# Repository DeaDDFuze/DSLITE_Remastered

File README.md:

# DSLITE_Remastered

> A modern hardware rework of the Nintendo DS Lite.

**DSLITE_Remastered** is an experimental hardware engineering project aiming to recreate and modernize the Nintendo DS Lite while preserving compatibility with the original console, cartridges, controls and overall form factor.

The goal is not to emulate a Nintendo DS on a modern computer.

The goal is to understand the original hardware, reverse-engineer it where necessary, redesign selected parts of the electronics, and progressively build a **modernized DS Lite around the original architecture**.

---

## Project goals

DSLITE_Remastered explores several areas of console hardware modernization:

- Reverse engineering of the Nintendo DS Lite motherboard
- Recreation of schematics in KiCad
- PCB analysis and eventual PCB redesign
- Replacement of ageing or obsolete components
- USB-C charging
- Modern battery and charging circuitry
- Improved power management
- Modern replacement displays
- Experimental display scaling / image processing
- Replacement shells and mechanical parts
- 3D CAD reconstruction of the console
- Improved repairability
- Hardware documentation
- Community-friendly component libraries

The project will remain modular so individual modifications can potentially be reproduced independently.

---

## Project philosophy

The idea behind DSLITE_Remastered is simple:

**repair, understand, reproduce, improve.**

Rather than replacing the entire console with a Raspberry Pi or an emulator, this project attempts to retain as much of the original Nintendo DS architecture as possible.

Whenever possible, the project will favor:

- original hardware compatibility;
- measurable and documented modifications;
- replaceable components;
- open design files;
- commonly available parts;
- reproducible modifications;
- preservation of the original console's behaviour.

Some parts of the project will necessarily remain experimental.

---

## Planned architecture

The long-term project may include several independent hardware modules.

### Main motherboard

Reverse engineering and recreation of the Nintendo DS Lite motherboard.

Current reference board:

`USG-CPU-10`

Objectives:

- reproduce the original schematic;
- identify component functions;
- document power rails;
- document buses and signals;
- recreate footprints;
- compare component revisions;
- prepare a possible redesigned motherboard.

---

### Power system

Potential improvements:

- USB-C connector;
- USB-C charging;
- modern Li-ion / Li-Po battery support;
- improved battery protection;
- improved charging controller;
- voltage monitoring;
- replaceable battery design.

USB Power Delivery is not currently required for the console but may be investigated for future accessories or docking concepts.

---

### Displays

One of the major experimental areas of the project.

Possible directions include:

- modern IPS LCD replacements;
- custom LCD interface boards;
- OLED experimentation;
- improved brightness;
- improved viewing angles;
- replacement backlight circuitry.

The native Nintendo DS resolution remains:

**256 × 192 pixels per screen**

A future experimental display controller may investigate integer scaling or real-time upscaling to higher-resolution panels.

---

## DS Remastered display concept

A more experimental branch of the project explores the concept of a **"DS Remastered" display pipeline**.

Instead of modifying the game software, a dedicated video-processing circuit could intercept the original display signal and process it before sending it to a modern panel.

Conceptually:

```text
Nintendo DS GPU
      │
      ▼
Original display signal
      │
      ▼
Video capture / interface
      │
      ▼
FPGA / video processor
      │
      ├── Integer scaling
      ├── Filtering
      ├── Pixel reconstruction
      └── Experimental upscaling
      │
      ▼
Modern LCD / OLED panel
```

The first realistic objective would be **clean integer scaling**, not AI-based reconstruction.

More advanced processing may be investigated later.

---

## Mechanical redesign

The mechanical side of the project will be developed primarily using **Fusion 360**.

Possible work includes:

- recreation of the DS Lite shell;
- internal mounting points;
- USB-C modifications;
- display adapters;
- replacement hinge mechanisms;
- battery compartment redesign;
- custom shells;
- prototype PCBs;
- 3D printable replacement parts.

KiCad remains the primary tool for electronic design.

---

## Software used

### Electronics

- KiCad
- SPICE simulation where appropriate
- Datasheets
- Multimeter
- Logic analyser
- Oscilloscope

### Mechanical design

- Autodesk Fusion 360
- Mesh / STEP / STL tools
- 3D printing

### Development / documentation

- Git
- GitHub
- Linux
- Markdown
- Python

---

## Repository structure

The repository will progressively follow a structure similar to:

```text
DSLITE_Remastered/
│
├── README.md
├── LICENSE
│
├── docs/
│   ├── architecture/
│   ├── reverse-engineering/
│   ├── measurements/
│   └── research/
│
├── datasheets/
│
├── schematic/
│   ├── original/
│   └── remastered/
│
├── pcb/
│   ├── original/
│   └── remastered/
│
├── libraries/
│   ├── symbols/
│   ├── footprints/
│   └── 3dmodels/
│
├── mechanical/
│   ├── shell/
│   ├── screen/
│   └── usb-c/
│
├── firmware/
│
├── tools/
│
└── references/
```

This structure may change as the project evolves.

---

## Current project status

**Status: Research / Reverse Engineering**

Current work focuses on:

- collecting DS Lite motherboard documentation;
- analysing the `USG-CPU-10` board revision;
- identifying components;
- collecting datasheets;
- reconstructing schematics;
- creating reusable KiCad symbols and footprints;
- preparing a clean Git repository structure.

No complete replacement motherboard exists yet.

---

## Roadmap

### Phase 1 — Documentation

- [ ] Photograph and document the motherboard
- [ ] Identify major ICs
- [ ] Identify passive components
- [ ] Collect datasheets
- [ ] Document test points
- [ ] Document connectors
- [ ] Map power rails

### Phase 2 — Schematic reconstruction

- [ ] Recreate `USG-CPU-10` schematics
- [ ] Verify connections
- [ ] Create missing KiCad symbols
- [ ] Create missing footprints
- [ ] Compare board revisions

### Phase 3 — PCB reconstruction

- [ ] Recreate PCB outline
- [ ] Position major components
- [ ] Reconstruct routing
- [ ] Validate dimensions
- [ ] Generate 3D PCB model

### Phase 4 — Modernization

- [ ] USB-C charging
- [ ] Modern battery circuitry
- [ ] Modern replacement displays
- [ ] Improved power circuitry
- [ ] Replacement shell design

### Phase 5 — DS Remastered experiments

- [ ] Capture original LCD signals
- [ ] Characterize timing
- [ ] Prototype FPGA display interface
- [ ] Integer-scale DS output
- [ ] Test higher-resolution panels
- [ ] Investigate image enhancement

### Phase 6 — Prototype

- [ ] Manufacture prototype PCBs
- [ ] Assemble board
- [ ] Power validation
- [ ] Boot testing
- [ ] Cartridge testing
- [ ] Touchscreen testing
- [ ] Wireless testing
- [ ] Long-term reliability testing

---

## Reverse engineering notes

All measurements and reverse-engineering information should be documented whenever possible.

Useful information includes:

```text
Component reference
Manufacturer
Part number
Package
Measured value
Connected signals
Voltage
Frequency
Datasheet
Board location
Notes
```

This repository should progressively become both a development repository and a technical reference for DS Lite hardware.

---

## KiCad libraries

One objective of the project is to create a reusable local KiCad library for DS Lite components.

Example:

```text
libraries/
├── symbols/
│   └── DSLITE_Remastered.kicad_sym
│
├── footprints/
│   └── DSLITE_Remastered.pretty/
│
└── 3dmodels/
    ├── STEP/
    └── WRL/
```

Components should preferably include:

- symbol;
- footprint;
- datasheet reference;
- manufacturer part number;
- package;
- pin description;
- 3D model when available.

---

## Contributions

Contributions are welcome.

Useful contributions include:

- board photographs;
- high-resolution scans;
- component identification;
- datasheets;
- PCB measurements;
- schematics;
- KiCad symbols;
- KiCad footprints;
- 3D models;
- electrical measurements;
- compatible replacement components;
- repair documentation.

Please document the source of technical information whenever possible.

---

## Disclaimer

DSLITE_Remastered is an independent, unofficial hardware research project.

Nintendo, Nintendo DS, Nintendo DS Lite and related trademarks are property of Nintendo and their respective owners.

This project is not affiliated with, endorsed by, or sponsored by Nintendo.

The repository is intended for:

- hardware research;
- repair;
- preservation;
- reverse engineering;
- education;
- experimentation.

No proprietary Nintendo software, firmware, ROMs or copyrighted game assets should be distributed through this repository.

---

## License

The final licensing model has not yet been selected.

Because the project may contain hardware designs, documentation and software, separate licenses may eventually be used for each category.

Possible choices include:

- CERN Open Hardware Licence for PCB and hardware designs
- GPL or MIT for software and tools
- Creative Commons for documentation

---

## Project name

**DSLITE_Remastered**

Experimental Nintendo DS Lite hardware modernization and preservation project.

```text
Original hardware.
Modern components.
Same DS.
```

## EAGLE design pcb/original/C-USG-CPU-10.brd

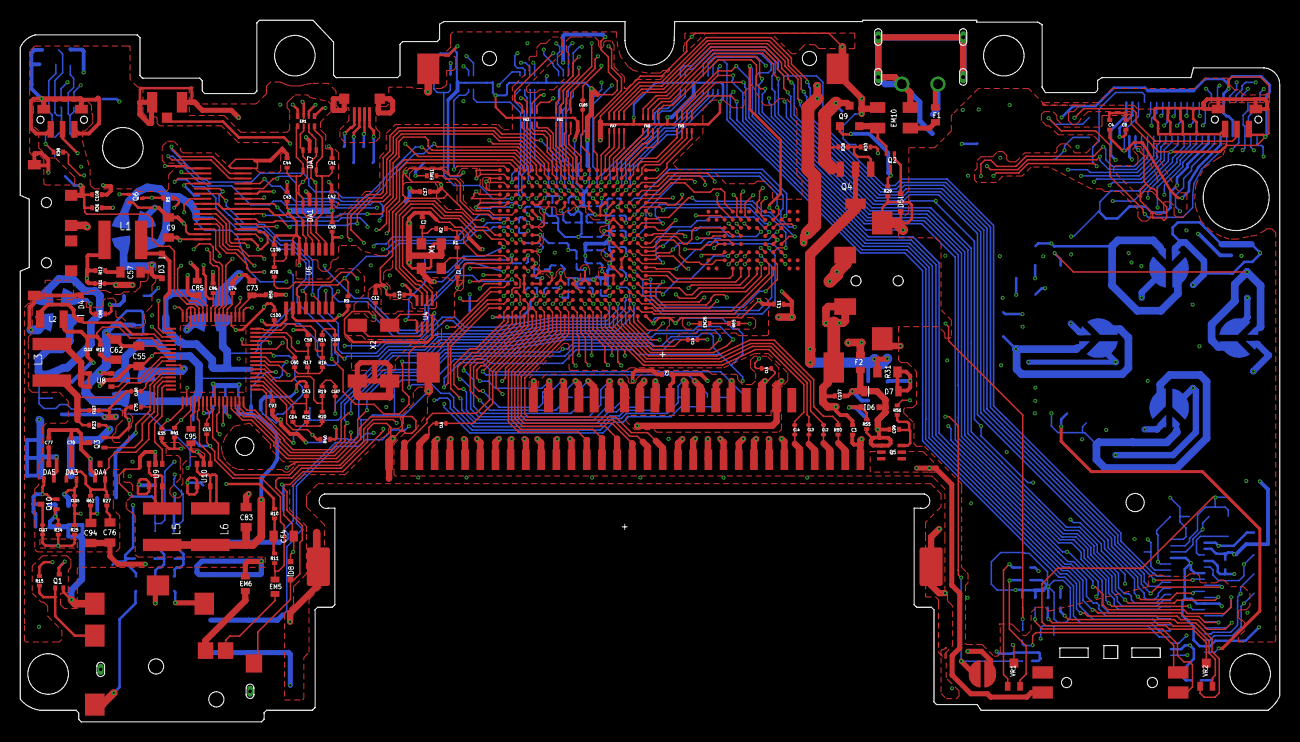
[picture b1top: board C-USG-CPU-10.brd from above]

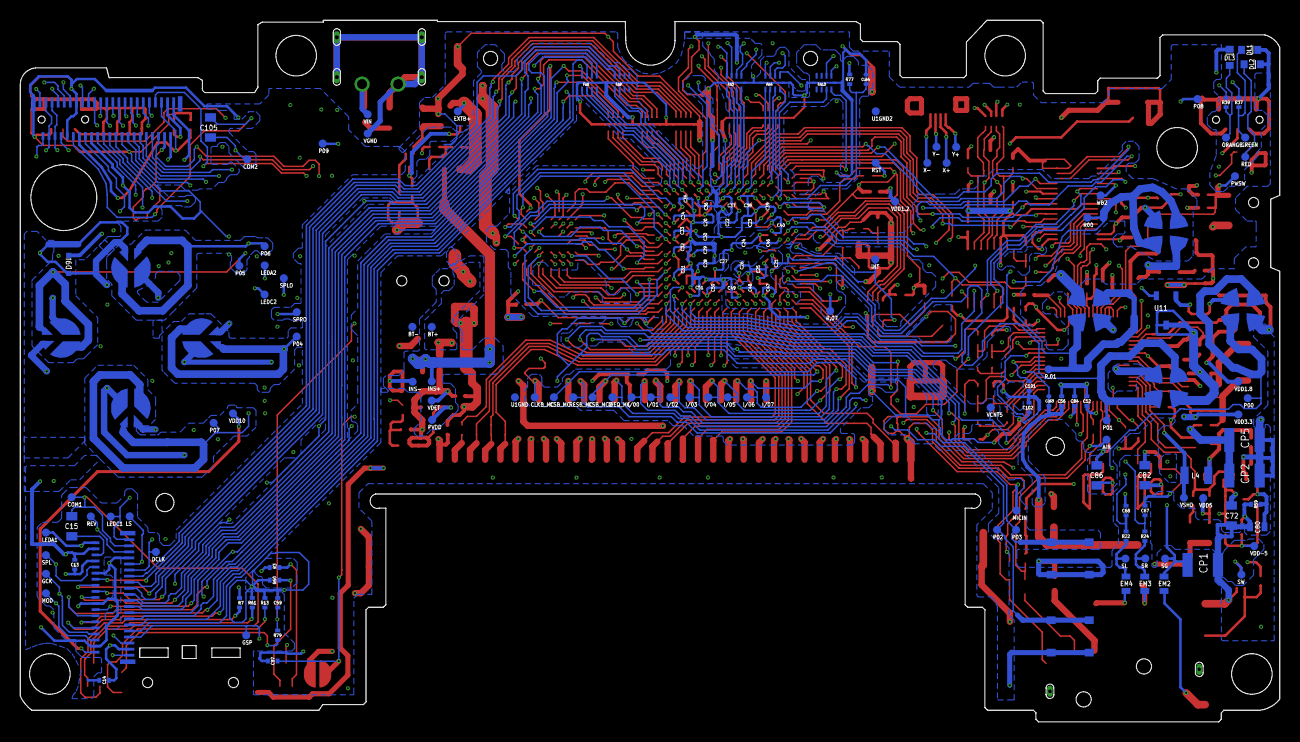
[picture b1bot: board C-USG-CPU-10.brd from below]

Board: 6 copper layers, 124.3 x 69.2 mm, 319 parts (164 on the bottom side), 328 nets.

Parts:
AIN: TP
BT+: TP
BT-: TP
BUT_A: BUT_ABXY; BUTTONSABXY
BUT_B: BUT_ABXY; BUTTONSABXY
BUT_L: SHOULDER_BUT
BUT_R: SHOULDER_BUT
BUT_X: BUT_ABXY; BUTTONSABXY
BUT_Y: BUT_ABXY; BUTTONSABXY
C1, C2, C3, C4, C5, C6, C10, C11, C12, C13, C14, C17, C41, C42, C43, C44, C45, C52, C53, C56, C58, C59, C60, C63, C64, C67, C68, C70, C74, C75, C77, C84, C88, C93, C96, C97, C99, C100, C101, C102, C106, C107, C108: C0402; 0402
C9, C15, C54, C55, C57, C62, C72, C76, C82, C83, C86, C94, C105: C0805; 0805
C20, C21, C22, C23, C24, C25, C26, C27, C28, C29, C30, C31, C32, C33, C34, C35, C36, C37, C38, C39, C40, C46, C47, C48, C49, C50, C51: C0201; 0201
C73, C80, C85, C95: C0603; 0603
CL2, CL3, CL4, CL5, CL6, CL9, CL11, CL12, CL13, CL15, CL17, CL60, CL63, CL64, CL65, CL67, CL68: CL; CL0402
CLKB_MC: TP
COM1, COM2: TP
CP1, CP2, CP5: CP
CSB_MC, CSB_MC2: TP
D3, D4: D3.4
D5, D9: D5
D6: D6
D7: D7
D8: D8
DA1: MA5J002D; DA
DA3, DA4, DA5: MA3SD29F
DA7: MA5J002E; DA
DCLK: TP
DL1, DL2, DL3: DL
DOWN: DPAD
EM1: FILTER_NETWORK
EM2, EM3, EM4, EM5, EM6: FILTER0603; 0603
EM10: EM10
EM11, EM26: FILTER; 0402
EXTB+: TP
F1, F2: FUSE
FA1, FA2, FA3, FA4, FA5, FA6, FA7, FA8, FA9, FA10: FA
GCK: TP
GREEN: TP
GSP: TP
I/00, I/01, I/02, I/03, I/04, I/05, I/06, I/07: TP
INS+: TP
INS-: TP
INT: TP
IREQ_MC: TP
L1, L3, L5, L6: INDUCTOR
L2, L4: INDUCTOR_SMALL
LEDA1, LEDA2: TP
LEDC1, LEDC2: TP
LEFT: DPAD
LS: TP
MICIN: TP
MOD: TP
ORANGE: TP
P00, P01, P02, P03, P04, P05, P06, P07, P08, P09: TP
P.1: GBASLOT; GBA
P.2: DSSLOT; DS
P.3: TOP_SCR+SPK
P.4: BOTTOM_SCREEN
P.6: TOUCH; P6
P.7: BAT
P.8: HEADPHONES
P.9: CHARGEPORT
P.10: DWM-W006; DWM--W006
P.12: MIC
PVDD: TP
PWSW: TP
Q1: Q1
Q2: DTA143ZM; SOT723
Q3, Q10: SSM3K16FS; Q3.10
Q4: 2SA2069; SOT89-3
Q5: SSM6J21TU; UF6
Q6: 2SC4244; SOT723
Q9: SSM3J14T; TO236
R00, R.01, R.07: TP
R1, R2, R3, R5, R7, R9, R10, R11, R12, R13, R14, R15, R16, R17, R18, R19, R20, R21, R22, R23, R24, R25, R27, R28, R29, R30, R34, R35, R36, R37, R38, R39, R40, R41, R50, R55, R56, R59, R60, R61, R62, R65, R77, R78, R79, R80: R0402; 0402
R31: R0805; 0805
RED: TP
RESB_MC: TP
REV: TP
RIGHT: DPAD
RST: TP
SELECT: BUTTON_SMALL
SG: TP
SL: TP
SL1: SL1
SPL: TP
SPLO: TP
SPRO: TP
SR: TP
START: BUTTON_SMALL
SW: TP
SW13: SWITCH
U1: NTR_CPU_B; CPU
U1GND, U1GND2: TP
U2: 82DBS02163C-70L; RAM
U3: MITSUMI_3325A
U4: RTC; TSSOP8
U6: TSC2046; TSSOP16
U8: SSM5G04TU; SOT-353F___(UFV)-M
U9, U10: SSM5H08TU; SOT-353F___(UFV)-M
U11: EM6781
UP: DPAD
VCNT5: TP
VDD1.2, VDD1.8, VDD3.3, VDD5, VDD10: TP
VDD-5: TP
VDET: TP
VGND: TP
VIN: TP
VR1, VR2: VR
VR3: VOLUME
VSHD: TP
WB2: TP
X1: X1
X2: X2
X+: TP
X-: TP
Y+: TP
Y-: TP

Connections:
A16: P.1.22, U1.G17
A17: P.1.23, U1.H17
A18: P.1.24, U1.I17
A19: P.1.25, U1.J17
A20: P.1.26, U1.K17
A21: P.1.27, U1.L17
A22: P.1.28, U1.M17
A23: P.1.29, U1.N17
AD0: P.1.6, U1.G18
AD1: P.1.7, U1.G19
AD2: P.1.8, U1.H18
AD3: P.1.9, U1.H19
AD4: P.1.10, U1.I18
AD5: P.1.11, U1.I19
AD6: P.1.12, U1.J18
AD7: P.1.13, U1.J19
AD8: P.1.14, U1.K18
AD9: P.1.15, U1.K19
AD10: P.1.16, U1.L18
AD11: P.1.17, U1.L19
AD12: P.1.18, U1.M18
AD13: P.1.19, U1.M19
AD14: P.1.20, U1.N18
AD15: P.1.21, U1.N19
AIN: AIN.P$1, C53.2, EM5.1, R11.2
AUX: R78.1, U3.40
B+: C55.1, C56.2, C83.1, CL63.1, CL63.2, L5.P$2, L6.P$2, Q5.1, Q5.2, Q5.5, Q5.6, U3.16, U3.19, U3.23, U3.55, U8.2, VR3.3
B.B0: FA6.1, P.4.22
B.B1: FA7.7, P.4.23
B.B2: FA7.5, P.4.24
B.B3: FA7.3, P.4.25
B.B4: FA7.1, P.4.26
B.B5: FA9.3, P.4.27
B.G0: FA8.7, P.4.15
B.G1: FA6.5, P.4.16
B.G2: FA6.7, P.4.17
B.G3: FA8.5, P.4.19
B.G4: FA9.1, P.4.20
B.G5: FA6.3, P.4.21
B.R0: FA8.3, P.4.9
B.R1: FA8.1, P.4.10
B.R2: FA5.7, P.4.11
B.R3: FA5.3, P.4.12
B.R4: FA5.5, P.4.13
B.R5: FA5.1, P.4.14
BT+: BT+.P$1, F2.1, P.7.+
CLKB_MC: CL5.1, CL5.2, CLKB_MC.P$1, P.2.2, U1.T16
COM1: C15.1, COM1.P$1, P.4.37, VR2.2
COM2: C105.1, COM2.P$1, P.3.37, VR1.2
CS1B: CL4.1, CL4.2, P.1.5, U1.F19
CS2B: CL6.1, CL6.2, P.1.30, U1.O18
CSB_MC: CSB_MC.P$1, P.2.4, U1.S17
CSB_MC2: CSB_MC2.P$1, P.2.6, U1.P17
DCLK: DCLK.P$1, P.3.29, P.4.29, U1.G1
EXTB+: EXTB+.P$1, Q4.3, Q9.3, R28.1, R50.1
GCK: GCK.P$1, P.3.8, P.4.8, U1.H3
GND: BT-.P$1, BUT_A.1, BUT_A.4, BUT_B.1, BUT_B.4, BUT_L.1, BUT_L.3, BUT_L.S1, BUT_L.S2, BUT_R.1, BUT_R.3, BUT_R.S1, BUT_R.S2, BUT_X.1, BUT_X.4, BUT_Y.1, BUT_Y.4, C1.1, C2.2, C3.2, C4.2, C5.2, C6.1, C9.2, C10.2, C11.1, C12.1, C13.2, C14.2, C17.2, C20.2, C21.2, C22.2, C23.2, C24.2, C25.2, C26.2, C27.2, C28.2, C29.2, C30.2, C31.2, C32.2, C33.2, C34.2, C35.2, C36.2, C37.2, C38.2, C39.2, C40.2, C41.1, C42.1, C43.1, C44.1, C45.1, C46.2, C47.2, C48.2, C49.2, C50.2, C51.2, C52.2, C54.2, C55.2, C56.1, C57.2, C58.2, C59.1, C62.2, C63.2, C67.2, C68.2, C72.1, C73.1, C74.1, C75.1, C76.2, C80.2, C82.1, C83.2, C84.1, C85.1, C86.1, C88.2, C93.1, C94.2, C95.1, C96.1, C97.1, C100.1, C101.2, C102.2, C106.1, C107.1, C108.1, CL64.1, CL64.2, CP1.1, CP2.1, CP5.1, D3.A, D4.A, D5.A, D8.A, D9.A, DA1.2, DA5.2, DL1.C, DL2.C, DL3.C, DOWN.1, DOWN.4, EM6.1, EM10.3, FA1.G1, FA1.G2, FA2.G1, FA2.G2, FA3.G1, FA3.G2, FA4.G1, FA4.G2, FA5.G1, FA5.G2, FA6.G1, FA6.G2, FA7.G1, FA7.G2, FA8.G1, FA8.G2, FA9.G1, FA9.G2, FA10.G1, FA10.G2, LEFT.1, LEFT.4, P.1.32, P.1.S1, P.1.S2, P.2.1, P.2.17, P.2.S1, P.2.S2, P.2.S3, P.2.S4, P.3.4, P.3.18, P.3.28, P.3.33, P.3.36, P.3.S2, P.4.4, P.4.18, P.4.28, P.4.33, P.4.36, P.6.S1, P.6.S2, P.7.-, P.7.S1, P.7.S2, P.8.4, P.10.1, P.10.6, P.10.9, P.10.13, P.10.15, P.10.17, P.10.23, P.10.30, P.12.G1, P.12.G2, Q1.2, Q3.2, Q6.2, Q10.1, R13.1, R29.2, R34.2, R35.2, R41.1, R59.2, R60.1, R61.1, R77.2, RIGHT.1, RIGHT.4, SELECT.2, SELECT.3, START.2, START.3, SW13.2, SW13.S1, SW13.S2, U1.A1, U1.A19, U1.D8, U1.D11, U1.D14, U1.E5, U1.E7, U1.E10, U1.E13, U1.F16, U1.G5, U1.G15, U1.I16, U1.J5, U1.J15, U1.L16, U1.M5, U1.M15, U1.O8, U1.O11, U1.O14, U1.O16, U1.O17, U1.P5, U1.P8, U1.P11, U1.P13, U1.R4, U1.R5, U1.R6, U1.S2, U1.S4, U1.S5, U1.T1, U1.T4, U1.T5, U1.T19, U1GND.P$1, U1GND2.P$1, U2.G2, U2.J8, U3.4, U3.13, U3.14, U3.15, U3.22, U3.26, U3.34, U3.41, U3.60, U4.4, U6.6, U6.7, U8.3, U9.2, U10.2, U11.3, UP.1, UP.4, X1.2, X1.4, X2.2, X2.3
GREEN: DL1.A, GREEN.P$1, R37.2
GSP: GSP.P$1, P.3.7, P.4.7, U1.H4
I/O0: I/00.P$1, P.2.9, U1.T17
I/O1: I/01.P$1, P.2.10, U1.T18
I/O2: I/02.P$1, P.2.11, U1.S18
I/O3: I/03.P$1, P.2.12, U1.S19
I/O4: I/04.P$1, P.2.13, U1.R18
I/O5: I/05.P$1, P.2.14, U1.R19
I/O6: I/06.P$1, P.2.15, U1.P18
I/O7: I/07.P$1, P.2.16, U1.P19
INS+: INS+.P$1, Q4.2, Q4.P, R31.2, U3.7
INS-: D7.A, INS-.P$1, R31.1, U3.8
INT: INT.P$1, U1.T10, U4.1
IREQ_MC: IREQ_MC.P$1, P.2.7, U1.R17
IRQ: P.1.31, U1.O19
LEDA1: C82.2, LEDA1.P$1, P.4.38, U9.4
LEDA2: C86.2, LEDA2.P$1, P.3.38, U10.4
LEDC1: LEDC1.P$1, P.4.39, R35.1, U3.33
LEDC2: D9.C, LEDC2.P$1, P.3.39, R41.2, U3.35
LS: LS.P$1, P.3.31, P.4.31, U1.H2
MICIN: D8.C, MICIN.P$1, P.8.7, P.12.M
MOD: MOD.P$1, P.3.6, P.4.6, U1.I2
unnamed: P.8.5, Q1.1, R15.1
unnamed: C95.2, U3.36
unnamed: C99.2, Q5.3, R56.1
unnamed: C70.2, DA3.3
unnamed: Q6.1, U11.2
unnamed: U1.B15, U2.G1
unnamed: C74.2, U3.5
unnamed: U1.C14, U2.F1
unnamed: C77.2, DA5.3
unnamed: C62.1, R18.2
unnamed: U1.A14, U2.E1
unnamed: EM3.2, P.8.3
unnamed: EM4.2, P.8.2
unnamed: R9.1, U1.R9, U6.11
unnamed: C67.1, R24.1, U3.56
unnamed: C68.1, R22.1, U3.59
unnamed: U1.B13, U2.D1
unnamed: R37.1, U3.43
unnamed: U1.C12, U2.F2
unnamed: U1.A12, U2.E2
unnamed: U1.C11, U2.D2
unnamed: U1.B10, U2.C2
unnamed: R56.2, U3.11
unnamed: U1.A10, U2.C6
unnamed: C58.1, R17.1, U3.63
unnamed: U1.C9, U2.E6
unnamed: C64.1, U3.52
unnamed: U1.A8, U2.F6
unnamed: FA8.4, U1.D3
unnamed: U1.E17, U6.15
unnamed: C93.2, U3.50
unnamed: U1.T9, U4.7
unnamed: C42.2, DA1.1, DA7.1, EM1.6, U6.3
unnamed: U1.C8, U2.C7
unnamed: U1.B7, U2.D7
unnamed: R80.1, U1.E18
unnamed: U4.2, X2.1
unnamed: C106.2, R78.2, U6.8
unnamed: C43.2, DA1.3, DA7.3, EM1.4, U6.4
unnamed: C44.2, DA1.4, DA7.4, EM1.2, U6.5
unnamed: U1.S10, U4.6
unnamed: C41.2, DA1.5, DA7.5, EM1.8, U6.2
unnamed: U1.R10, U4.5
unnamed: C12.2, U4.3, X2.4
unnamed: R1.1, R2.2, U1.S12
unnamed: C1.2, R1.2, U1.T12, X1.3
unnamed: P.10.29, U1.P1
unnamed: C2.1, R2.1, X1.1
unnamed: P.10.21, U1.P2
unnamed: P.10.19, U1.R1
unnamed: P.10.2, U1.O2
unnamed: P.10.3, U1.N3
unnamed: P.10.4, U1.N4
unnamed: P.10.5, U1.N2
unnamed: P.10.7, U1.N1
unnamed: U1.A6, U2.E7
unnamed: P.10.8, U1.O1
unnamed: U1.A5, U2.F7
unnamed: P.10.20, U1.L2
unnamed: U1.A4, U2.D8
unnamed: U1.C5, U2.G8
unnamed: U1.A3, U2.F3
unnamed: U1.B4, U2.E3
unnamed: U1.B3, U2.D6
unnamed: C63.1, R21.1, U3.53
unnamed: U1.C4, U2.E5
unnamed: U1.C3, U2.E8
unnamed: U1.A15, U2.J2
unnamed: EM10.2, F1.1
unnamed: Q2.3, Q9.1, R29.1
unnamed: C52.1, R10.1, U3.38
unnamed: U1.B14, U2.G3
unnamed: U1.A13, U2.K3
unnamed: P.10.10, U1.M4
unnamed: C70.1, C77.1, DA4.1, L4.2, Q3.3
unnamed: FA8.2, U1.D4
unnamed: P.10.11, U1.M2
unnamed: P.10.18, U1.M1
unnamed: U1.C13, U2.H4
unnamed: P.10.12, U1.L3
unnamed: C73.2, R50.2, U3.2
unnamed: P.10.14, U1.M3
unnamed: EM11.2, U1.T7
unnamed: FA5.8, U1.A2
unnamed: U1.B12, U2.H5
unnamed: FA5.4, U1.B1
unnamed: FA5.6, U1.B2
unnamed: FA5.2, U1.C2
unnamed: U1.B11, U2.K6
unnamed: FA8.8, U1.E3
unnamed: FA6.6, U1.D2
unnamed: U1.A11, U2.G6
unnamed: FA6.8, U1.C1
unnamed: FA8.6, U1.E4
unnamed: FA9.2, U1.F3
unnamed: R39.1, U3.3
unnamed: U1.C10, U2.J7
unnamed: FA6.4, U1.D1
unnamed: C54.1, R10.2, R11.1
unnamed: U1.B9, U2.K2
unnamed: Q3.1, U3.29
unnamed: C53.1, U3.39
unnamed: U1.A9, U2.H3
unnamed: U1.B8, U2.J3
unnamed: U1.A7, U2.K4
unnamed: C64.2, R20.1, R21.2
unnamed: U1.C7, U2.J6
unnamed: FA6.2, U1.E2
unnamed: FA7.8, U1.E1
unnamed: FA7.6, U1.F2
unnamed: FA7.4, U1.F1
unnamed: FA7.2, U1.G2
unnamed: FA9.4, U1.G3
unnamed: FA1.8, U1.I1
unnamed: FA1.6, U1.I3
unnamed: FA3.2, U1.I4
unnamed: R13.2, VR3.1
unnamed: U1.B6, U2.H6
unnamed: U1.C6, U2.K7
unnamed: D5.C, Q2.1
unnamed: EM10.1, Q2.2, Q9.2
unnamed: Q4.1, R28.2, R30.2
unnamed: U1.B5, U2.H7
unnamed: FA1.2, U1.J2
unnamed: U1.B18, U2.J1
unnamed: C59.2, R79.1, U3.61
unnamed: FA1.4, U1.J1
unnamed: U1.B17, U2.D5
unnamed: U1.A18, U2.H2
unnamed: U1.B16, U2.C5
unnamed: U1.A17, U2.C3
unnamed: U1.A16, U2.D3
unnamed: FA3.4, U1.J3
unnamed: FA3.6, U1.J4
unnamed: FA2.2, U1.K4
unnamed: FA2.8, U1.K1
unnamed: FA2.6, U1.K2
unnamed: U1.C15, U2.D4
unnamed: EM26.1, U1.C16
unnamed: EM26.2, R65.1
unnamed: R65.2, U2.C4
unnamed: FA3.8, U1.K3
unnamed: FA4.2, U1.L4
unnamed: FA2.4, U1.L1
unnamed: R7.1, VR2.1
unnamed: FA4.4, U1.O3
unnamed: FA4.6, U1.O4
unnamed: FA10.6, U1.R2
unnamed: FA10.8, U1.S1
unnamed: FA4.8, U1.P4
unnamed: C15.2, P.4.34
unnamed: R61.2, VR2.3
unnamed: R3.1, VR1.1
unnamed: C105.2, P.3.34
unnamed: R60.2, VR1.3
unnamed: R19.1, R20.2, U3.54
unnamed: CL67.1, CL67.2, R19.2, U1.D16
unnamed: C60.2, R16.1, R17.2
unnamed: C60.1, U3.62
unnamed: R14.1, R16.2, U3.64
unnamed: CL68.1, CL68.2, R14.2, U1.D17
unnamed: R79.2, VR3.2
unnamed: U3.31, U9.1
unnamed: U3.37, U10.1
unnamed: L5.P$1, U9.3, U9.5
unnamed: R38.1, U3.42
unnamed: L6.P$1, U10.3, U10.5
unnamed: EM6.2, P.8.8
unnamed: EM5.2, P.8.6
unnamed: R30.1, U3.6
unnamed: C80.1, DA5.1, Q10.2, R59.1
unnamed: DA3.1, DA4.2, R27.1, R62.1, U3.30
unnamed: C76.1, R27.2
unnamed: L3.P$2, U8.4, U8.5
unnamed: CP2.2, CP5.2, R23.1
unnamed: U3.24, U8.1
unnamed: D4.C, L2.2, U3.20
unnamed: C57.1, R12.2
unnamed: D3.C, L1.P$2, U3.17
ORANGE: DL3.A, ORANGE.P$1, R39.2
P00: BUT_A.2, BUT_A.3, P00.P$1, U1.S16
P01: BUT_B.2, BUT_B.3, P01.P$1, U1.R15
P02: P02.P$1, SELECT.1, SELECT.4, U1.S15
P03: P03.P$1, START.1, START.4, U1.T15
P04: P04.P$1, RIGHT.2, RIGHT.3, U1.R14
P05: LEFT.2, LEFT.3, P05.P$1, U1.S14
P06: P06.P$1, U1.T14, UP.2, UP.3
P07: DOWN.2, DOWN.3, P07.P$1, U1.R13
P08: BUT_R.2, P08.P$1, U1.S13
P09: BUT_L.2, P09.P$1, U1.T13
PHI: P.1.2, R80.2
PHONES.GND: EM2.2, P.8.1
PVDD: C10.1, C85.2, D6.C, PVDD.P$1, R36.1, R55.1, U3.10, U4.8
PWSW: C108.2, PWSW.P$1, R36.2, SW13.1, U3.12
R00: BUT_X.2, BUT_X.3, R00.P$1, U1.S7
R.01: BUT_Y.2, BUT_Y.3, R.01.P$1, U1.R7
R.07: Q6.3, R5.1, R.07.P$1, U1.B19, U1.S9
RDB: CL3.1, CL3.2, P.1.4, U1.F18
RED: DL2.A, R38.2, RED.P$1
RESB_MC: P.2.5, RESB_MC.P$1, U1.R16
REV: CL65.1, CL65.2, P.3.35, P.4.35, REV.P$1, U1.H1
RST: EM11.1, P.10.22, R40.1, RST.P$1, U3.51
SG: CP1.2, EM2.1, P.3.42, P.3.43, SG.P$1
SL: EM4.1, R22.2, SL.P$1
SPI_C1: U1.C18, U3.48
SPI_C2: P.10.28, U1.D18
SPI_MISO: P.10.26, U1.D19, U3.47, U6.12
SPI_MOSI: P.10.25, U1.F17, U3.46, U6.14
SPI_SK: CL9.1, CL9.2, P.10.24, U1.C19, U3.45, U6.16
SPL: P.3.30, P.4.30, SPL.P$1, U1.G4
SPLO: C102.1, P.3.44, P.3.45, SPLO.P$1, U3.58
SPRO: C101.1, P.3.40, P.3.41, SPRO.P$1, U3.57
SR: EM3.1, R24.2, SR.P$1
SW: Q1.3, SW.P$1, U3.1
T.B0: FA2.3, P.3.22
T.B1: FA4.3, P.3.23
T.B2: FA4.5, P.3.24
T.B3: FA10.5, P.3.25
T.B4: FA10.7, P.3.26
T.B5: FA4.7, P.3.27
T.G0: FA3.5, P.3.15
T.G1: FA2.1, P.3.16
T.G2: FA2.7, P.3.17
T.G3: FA2.5, P.3.19
T.G4: FA3.7, P.3.20
T.G5: FA4.1, P.3.21
T.R0: FA1.7, P.3.9
T.R1: FA1.5, P.3.10
T.R2: FA3.1, P.3.11
T.R3: FA1.1, P.3.12
T.R4: FA1.3, P.3.13
T.R5: FA3.3, P.3.14
VCNT5: U1.C17, U3.49, VCNT5.P$1
VDD1.2: C17.1, C20.1, C21.1, C22.1, C23.1, C24.1, C25.1, C26.1, C27.1, C28.1, C29.1, C30.1, CL11.1, CL11.2, L1.P$1, R12.1, U1.E6, U1.E8, U1.E9, U1.E11, U1.E12, U1.E14, U1.E15, U1.F5, U1.F15, U1.H5, U1.H15, U1.I15, U1.K5, U1.K15, U1.L15, U1.N15, U1.O6, U1.O9, U1.O10, U1.O12, U1.O13, U1.O15, U1.P12, U3.18, VDD1.2.P$1
VDD1.8: C11.2, C31.1, C32.1, C33.1, C34.1, CL12.1, CL12.2, L2.1, R18.1, U1.D7, U1.D9, U1.D10, U1.D12, U1.D13, U1.D15, U2.J4, U2.J5, U3.21, VDD1.8.P$1
VDD3.3: C3.1, C5.1, C9.1, C35.1, C36.1, C37.1, C38.1, C39.1, C40.1, C45.2, C46.1, C47.1, C48.1, C49.1, C50.1, C51.1, C84.2, C88.1, C100.2, CL13.1, CL13.2, CL60.1, CL60.2, DA7.2, L3.P$1, P.1.1, P.2.8, P.10.16, R5.2, R9.2, R15.2, R23.2, R40.2, R77.1, SL1.P$2, U1.D5, U1.D6, U1.E16, U1.F4, U1.G16, U1.H16, U1.I5, U1.J16, U1.K16, U1.L5, U1.M16, U1.N5, U1.N16, U1.O5, U1.O7, U1.P3, U1.P9, U1.P10, U1.P14, U1.P15, U1.P16, U1.S3, U1.T2, U3.25, U3.27, U3.44, U6.1, U6.9, U6.10, U11.1, VDD3.3.P$1
VDD5: C6.2, C14.1, C94.1, P.3.3, P.4.3, R3.2, R7.2, R62.2, VDD5.P$1
VDD10: C72.2, CL15.1, CL15.2, DA3.2, P.3.2, P.4.2, R25.1, VDD10.P$1
VDD-5: CL17.1, CL17.2, P.3.1, P.4.1, Q10.3, R25.2, R34.1, VDD-5.P$1
VDET: C96.2, C99.1, C107.2, D6.A, D7.C, F2.2, Q5.4, R55.2, U3.9, VDET.P$1
VGND: EM10.4, P.9.-, P.9.S1, P.9.S2, P.9.S3, P.9.S4, VGND.P$1
VIN: F1.2, P.9.+, VIN.P$1
VSHD: C4.1, C13.1, C75.2, L4.1, P.3.5, P.3.32, P.4.5, P.4.32, U3.28, VSHD.P$1
WB2: C97.2, P.10.27, SL1.P$1, WB2.P$1
WRB: CL2.1, CL2.2, P.1.3, U1.E19
X+: EM1.7, P.6.3, X+.P$1
X-: EM1.3, P.6.1, X-.P$1
Y+: EM1.5, P.6.4, Y+.P$1
Y-: EM1.1, P.6.2, Y-.P$1
